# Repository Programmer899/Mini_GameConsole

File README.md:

# Mini_GameConsole
## Description
This is a small mini GameConsole that you can play a few games on.
It has a joystick with a button, A and B buttons, Start and reset buttons, display and a piezo to make sound and effects.

The firmware is custom and built in C with the pico sdk.

## Schematic

## PCB

## Render

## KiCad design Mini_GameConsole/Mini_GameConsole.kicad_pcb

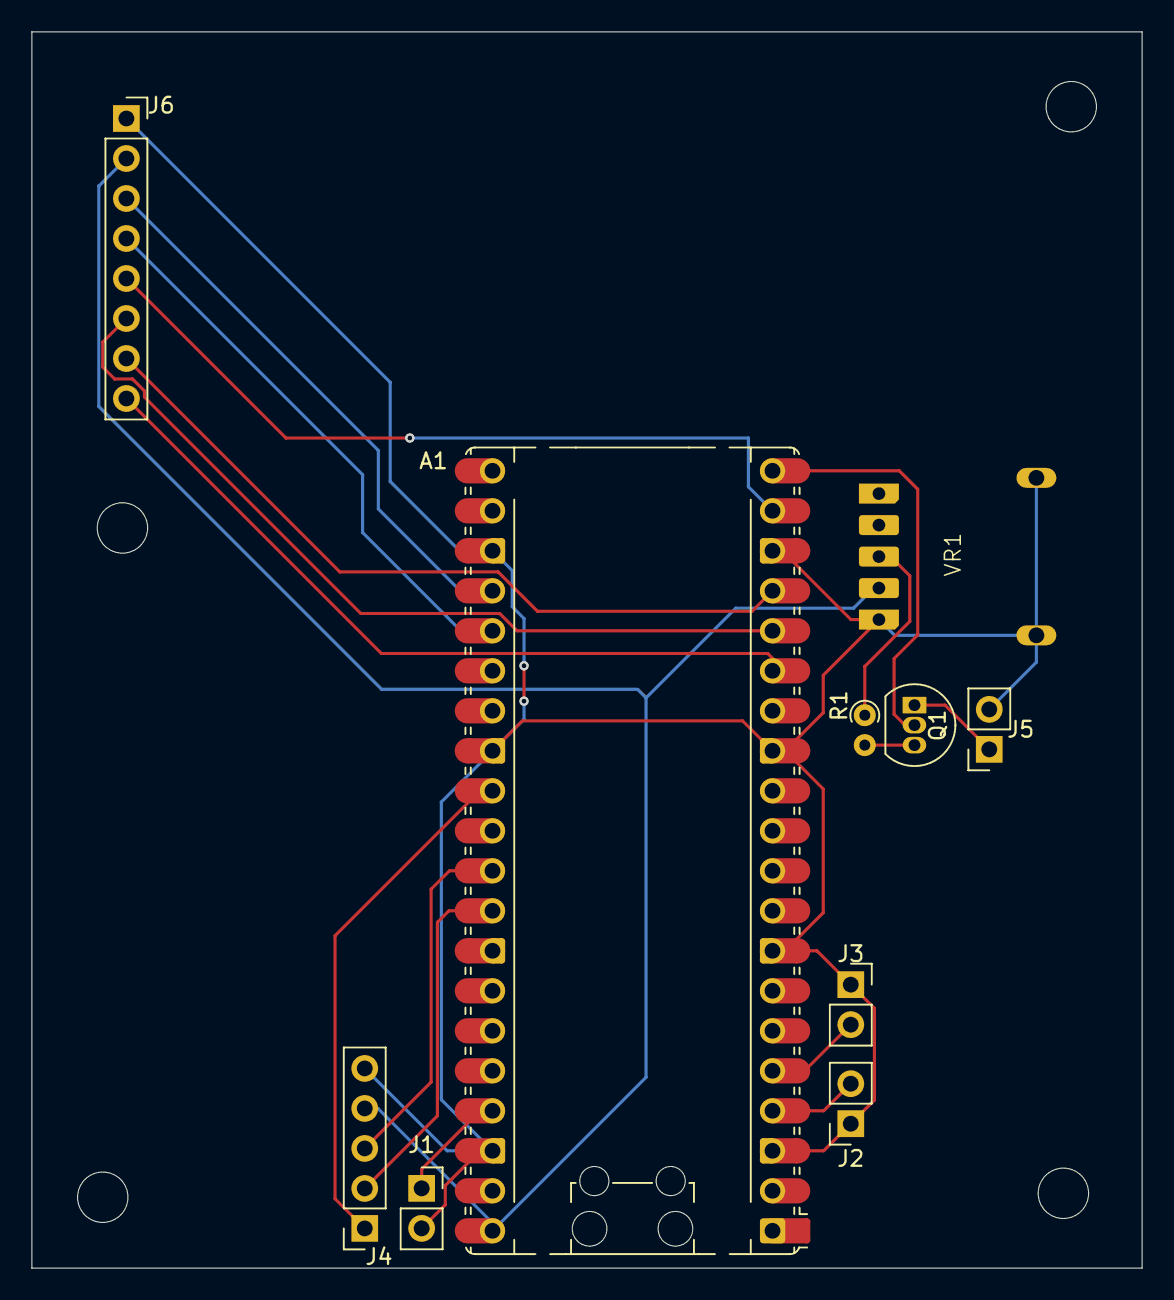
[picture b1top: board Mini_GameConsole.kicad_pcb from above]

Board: 2 copper layers, 70.5 x 78.5 mm, 10 parts (0 on the bottom side), 18 nets.

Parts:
A1: RaspberryPi_Pico; RaspberryPi_Pico_Common_Unspecified
J1: Conn_01x02_Socket; PinSocket_1x02_P2.54mm_Vertical
J2: AButton; PinSocket_1x02_P2.54mm_Vertical
J3: BButton; PinSocket_1x02_P2.54mm_Vertical
J4: Joystick; PinSocket_1x05_P2.54mm_Vertical
J5: Piezo; PinSocket_1x02_P2.54mm_Vertical
J6: Display; PinSocket_1x08_P2.54mm_Vertical
Q1: 2N3904; TO-92_Inline
R1: R; R_Axial_DIN0204_L3.6mm_D1.6mm_P1.90mm_Vertical
VR1: 5-Pin 16mm (Thumbwheel) Rotary Gear Potentiometer

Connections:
AButton Out: A1.4 (GPIO2), J2.2
BButton Out: A1.5 (GPIO3), J3.2
BL: A1.15 (GPIO11), J6.8
CS: A1.17 (GPIO13), J6.7
DC: A1.16 (GPIO12), J6.6
GND: A1.3 (GND), A1.8 (GND), A1.13 (GND), A1.18 (GND), A1.23 (GND), A1.28 (GND), A1.38 (GND), J1.2, J2.1, J3.1, J4.5, J5.2, J6.1, VR1.1, VR1.G (GND)
Joystick Button: A1.29 (GPIO22), J4.1
Joystick X-Axis: A1.31 (GPIO26_ADC0), J4.3
Joystick Y-Axis: A1.32 (GPIO27_ADC1), J4.2
unnamed: Q1.3 (C), R1.2
unnamed: R1.1, VR1.3
PIEZO+: J5.1, Q1.1 (E)
PWM TONE: A1.20 (GPIO15), Q1.2 (B)
RES: A1.19 (GPIO14), J6.5
RESET: A1.37 (3V3_EN), J1.1
SCL: A1.24 (GPIO18), J6.3
SDA: A1.25 (GPIO19), J6.4
VCC: A1.40 (VBUS), J4.4, J6.2, VR1.2
